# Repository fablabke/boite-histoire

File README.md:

> [!IMPORTANT]
> Attention, le logiciel de ce projet est en version beta, toute aide serait la bienvenue afin de le rendre plus robuste.

## Boite à histoire

Une boite à histoire complètement open source et open hardware, un projet du Fablab'ke.

Il existe sur le marché une série de “boîtes à histoires” qui permettent aux enfants d’écouter des histoires en audio. C’est un système qui fonctionne très bien et permet d’éviter les écrans tout en découvrant des univers assez variés. Écouter des histoires permet aussi de développer le langage et l’imaginaire.

Il y a par exemple la [boîte Lunii](https://lunii.com/fr-be/) et [pleins d’autres modèles](https://www.madmoizelle.com/quelles-sont-les-meilleures-boites-a-histoires-pour-les-enfants-1392363)

L’inconvénient majeur de toutes ces boîtes est le coût élevé de l’appareil (entre 70 et 100 euros) et le coût des packs d’histoires (une dizaine d’euros à chaque fois que l’on veut ajouter quelques histoires sur sa boîte sans pouvoir les partager avec d’autres).

Un autre inconvénient est que les bibliothèques d’histoires sont spécifiques à chaque fabricant, avec un contenu souvent assez lisse et peu multiculturel.

Nous avons décidé au Fablab'ke de développer et de fabriquer “notre” boîte à histoire maison, de créer en partenariat avec les autres cellules de la maison des cultures plusieurs projets autour de celle-ci, et d’en faire bénéficier les familles de la maison des cultures et au-delà.

Cette boite à histoire permet d'y installer autant d'histoire qu'on le souhaite, sans devoir passer par un "app-store" et permet du coup d'inventer et de se partager des histoires entre participant.e.s.

Une première série de 30 boites à histoire a été construite avec les classes d'informatique de Campus Saint Jean.

Ce projet est en cours de conception. [Contactez le fablab'ke](https://fablabke.be) pour plus d'informations.

## Mais comment fabriquer sa boite à histoire?

Lisez les documents suivants afin de comprendre les différentes étapes de fabrication et comment fabriquer la vôtre : 

- Principe de fonctionnement (todo)
- Carte électronique chez Aisler (todo)
- [Assemblage de la carte électronique](./guides/pcb.md)
- Code source arduino, facilement compilable avec platformio ou l'ide arduino : [/dossier arduino](./arduino)
- Code circuitpython (todo)

## Liste des composants nécessaires
- une plaquette d'expérimentation ou le circuit imprimé que l'on peut commander en ligne chez aisler.
- carte raspberry pi pico
- carte ampli i2s adafruit https://www.adafruit.com/product/3006 (clone : https://www.aliexpress.com/item/1005005985389931.html )
- carte chargeur (si vous voulez connecter une batterie) https://www.aliexpress.com/item/1005005982385924.html
- carte breakout sd adafruit : https://www.adafruit.com/product/4682
- potentiometre à souder trough hole 10k (par exemple : https://www.mouser.fr/ProductDetail/Same-Sky/PTN16-A10220K1B1?qs=VJzv269c%252BPbZP2voFoR5Tw%3D%3D )
- prise jack pour casque de ce type : https://www.mouser.be/ProductDetail/Same-Sky/SJ1-3525NG-GR?qs=WyjlAZoYn51BeLQaUbXH3w%3D%3D
- 3 résistances de 100k

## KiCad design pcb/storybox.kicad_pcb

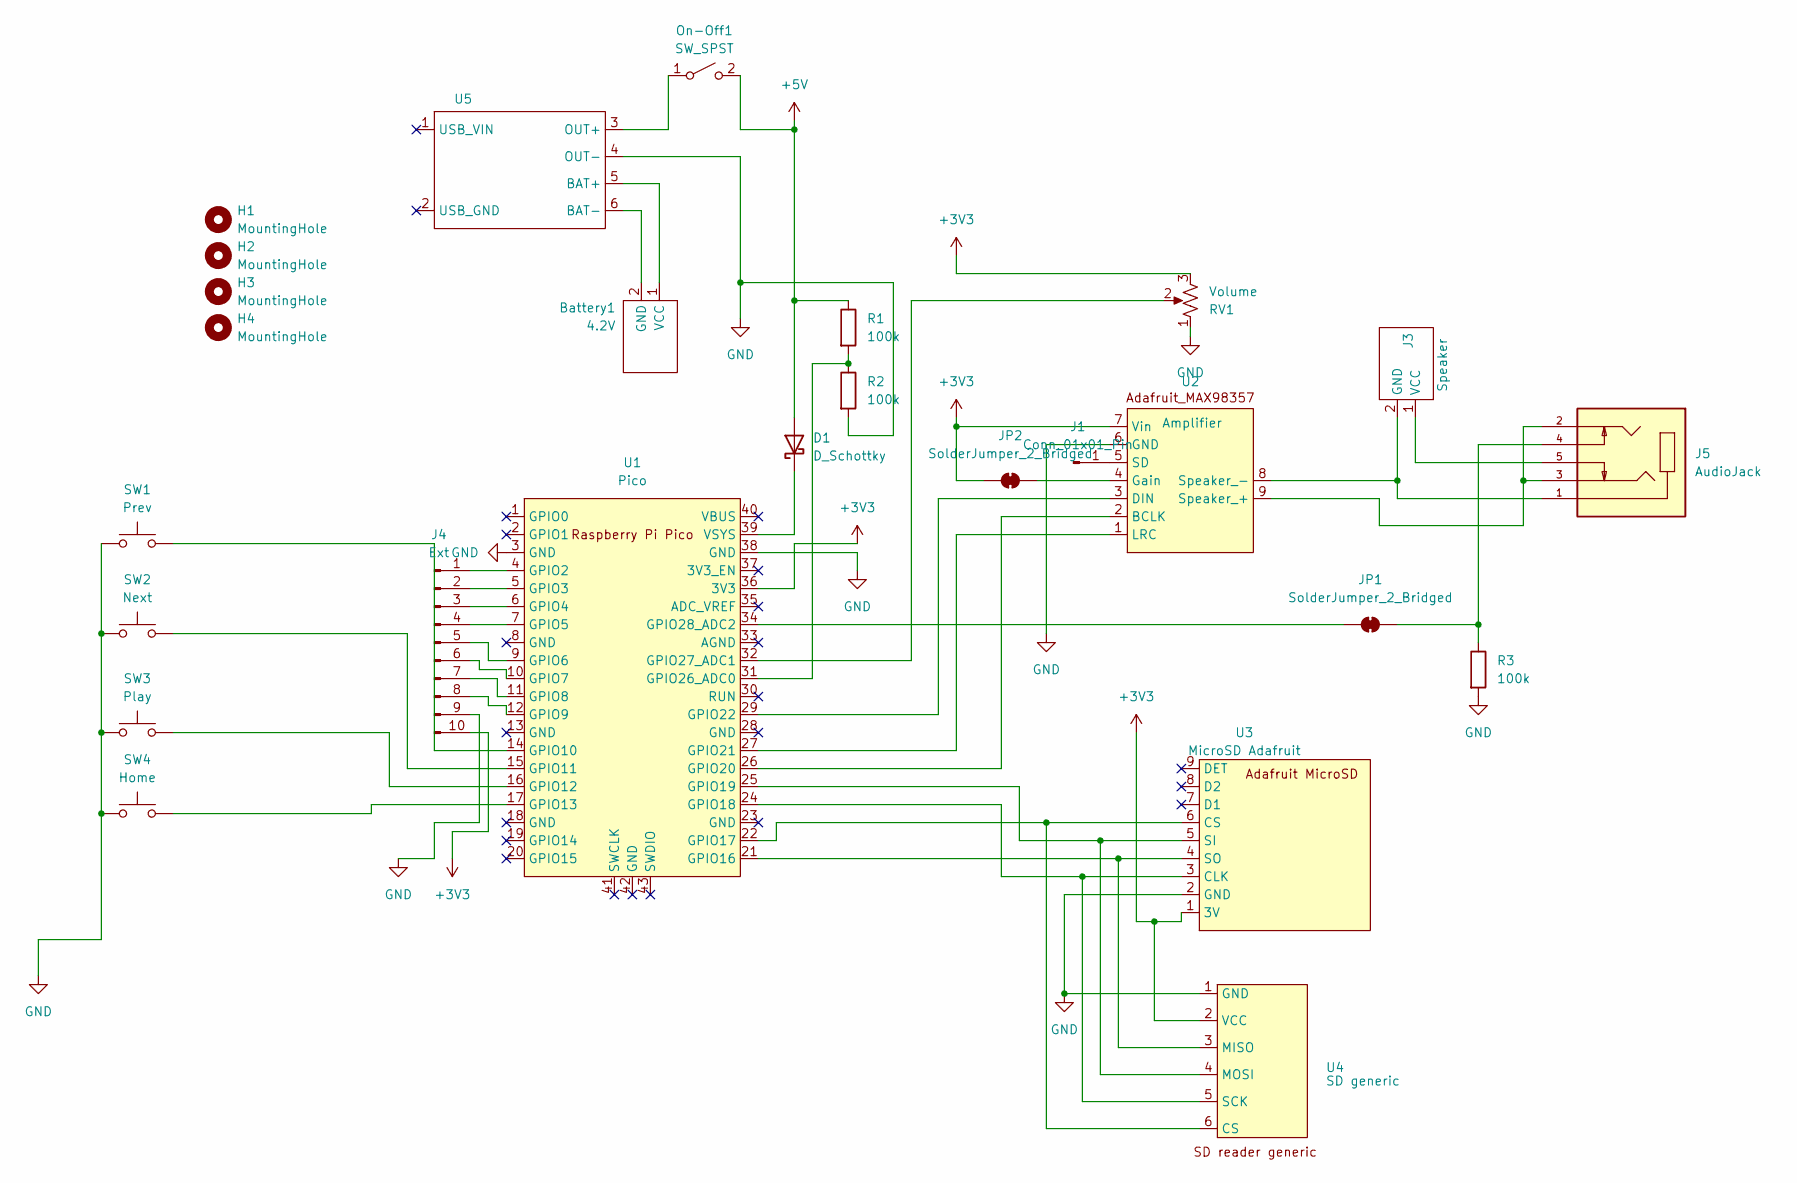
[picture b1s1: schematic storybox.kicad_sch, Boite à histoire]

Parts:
Battery1: 4.2V; connector_polarized
D1: D_Schottky; D_DO-15_P10.16mm_Horizontal
H1, H2, H3, H4: MountingHole; MountingHole_3.2mm_M3
J1: Conn_01x01_Pin; PinHeader_1x01_P2.54mm_Vertical
J3: Speaker; connector_polarized
J4: Ext; PinHeader_2x05_P2.54mm_Vertical
J5: AudioJack; CUI_SJ1-3525NG-GR
JP1, JP2: SolderJumper_2_Bridged; SolderJumper-2_P1.3mm_Bridged_Pad1.0x1.5mm
On-Off1: SW_SPST; connector_polarized
R1, R2, R3: 100k; R_Axial_DIN0204_L3.6mm_D1.6mm_P2.54mm_Vertical
RV1: Volume; Potentiometer_Alps_RK163_Single_Horizontal
SW1: Prev; SW_PUSH-12mm
SW2: Next; SW_PUSH-12mm
SW3: Play; SW_PUSH-12mm
SW4: Home; SW_PUSH-12mm
U1: Pico; RPi_Pico_SMD_TH
U2: Amplifier; Adafruit_MAX98357
U3: MicroSD Adafruit; Adafruit_MicroSd_3v
U4: SD generic; sd_reader_generic
U5: tp4056

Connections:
+3V3: J4.10, JP2.1 (A), RV1.3, U1.36 (3V3), U2.7 (Vin), U3.1 (3V), U4.2 (VCC)
+5V: D1.2 (A), On-Off1.2 (B), R1.1
GND: J4.9, R2.2, R3.2, RV1.1, SW1.2, SW2.2, SW3.2, SW4.2, U1.3 (GND), U1.38 (GND), U2.6 (GND), U3.2 (GND), U4.1 (GND), U5.4 (OUT-)
unnamed: D1.1 (K), U1.39 (VSYS)
unnamed: J1.1, U2.5 (SD)
unnamed: J3.1, J5.5
unnamed: J3.2, J5.1, U2.8 (Speaker_-)
unnamed: J4.1, U1.4 (GPIO2)
unnamed: J4.2, U1.5 (GPIO3)
unnamed: J4.3, U1.6 (GPIO4)
unnamed: J4.4, U1.7 (GPIO5)
unnamed: J4.5, U1.9 (GPIO6)
unnamed: J4.6, U1.10 (GPIO7)
unnamed: J4.7, U1.11 (GPIO8)
unnamed: J4.8, U1.12 (GPIO9)
unnamed: JP1.1 (A), U1.34 (GPIO28_ADC2)
unnamed: J5.4, JP1.2 (B), R3.1
unnamed: JP2.2 (B), U2.4 (Gain)
unnamed: On-Off1.1 (A), U5.3 (OUT+)
unnamed: SW1.1, U1.14 (GPIO10)
unnamed: SW2.1, U1.15 (GPIO11)
unnamed: SW3.1, U1.16 (GPIO12)
unnamed: SW4.1, U1.17 (GPIO13)
unnamed: U1.21 (GPIO16), U3.4 (SO), U4.3 (MISO)
unnamed: U1.22 (GPIO17), U3.6 (CS), U4.6 (CS)
unnamed: U1.24 (GPIO18), U3.3 (CLK), U4.5 (SCK)
unnamed: U1.25 (GPIO19), U3.5 (SI), U4.4 (MOSI)
unnamed: U1.26 (GPIO20), U2.2 (BCLK)
unnamed: U1.27 (GPIO21), U2.1 (LRC)
unnamed: U1.29 (GPIO22), U2.3 (DIN)
unnamed: R1.2, R2.1, U1.31 (GPIO26_ADC0)
unnamed: RV1.2, U1.32 (GPIO27_ADC1)
unnamed: J5.2, J5.3, U2.9 (Speaker_+)
unnamed: Battery1.1 (VCC), U5.5 (BAT+)
unnamed: Battery1.2 (GND), U5.6 (BAT-)

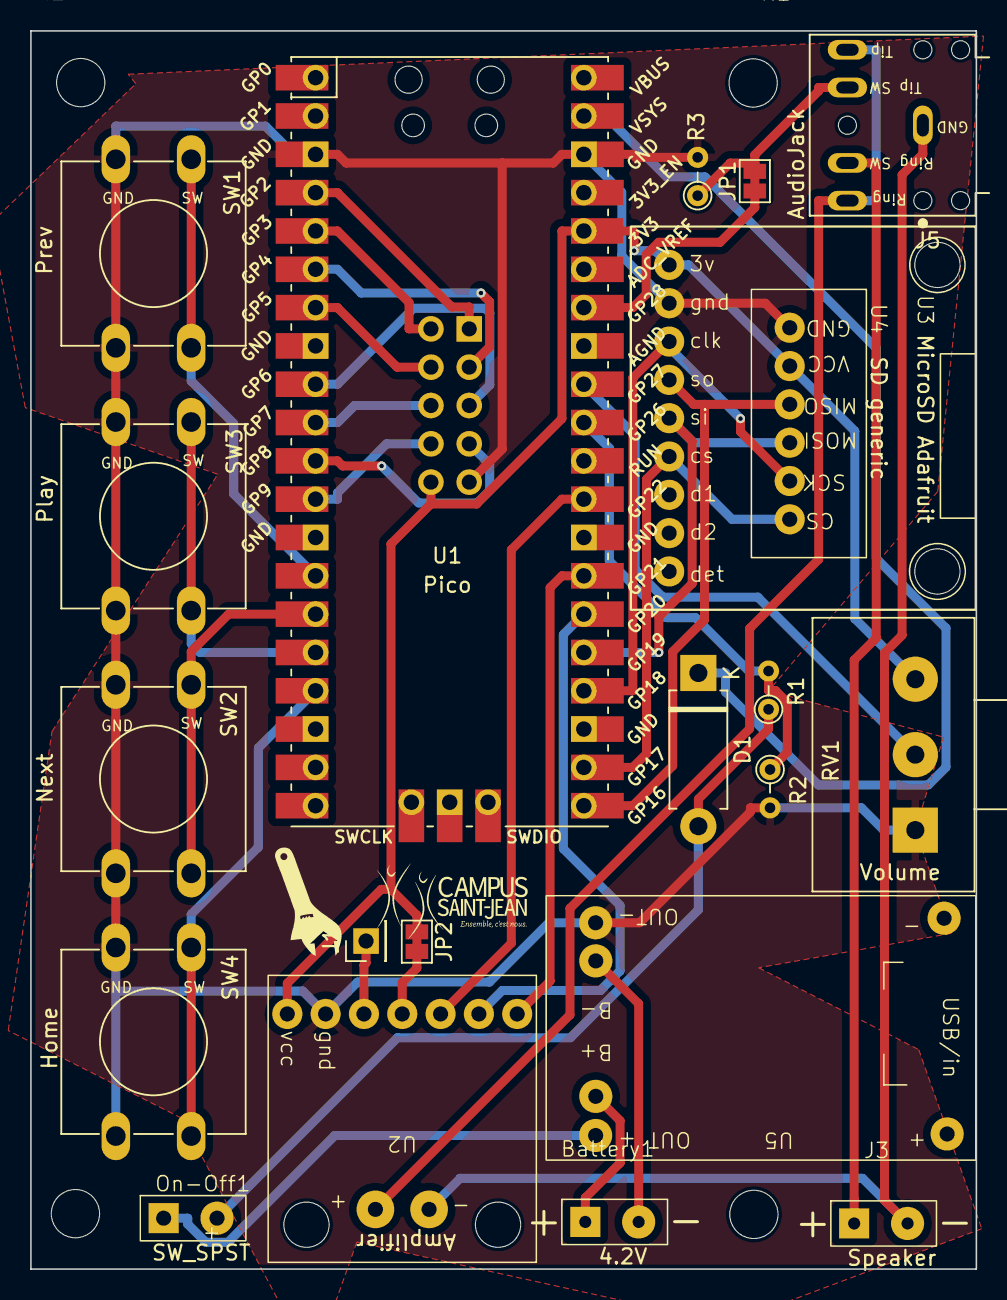
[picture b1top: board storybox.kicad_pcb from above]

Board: 2 copper layers, 62.7 x 82.1 mm, 26 parts (1 on the bottom side), 35 nets.

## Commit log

2024-05-29 up readme
2024-05-29 un petit visuel tout moche pour dire
2024-08-19 dernière version de la pcb + schéma
2024-08-19 dernière version du code arduino
2024-08-19 ajout photo
2025-04-22 Update README.md with bom
2026-02-26 Update README with beta software warning
    Added a warning about the software being in beta and requested assistance.
2026-05-10 update code to work with latest adio tools lib
2026-05-10 simplier test code using audiotools player
